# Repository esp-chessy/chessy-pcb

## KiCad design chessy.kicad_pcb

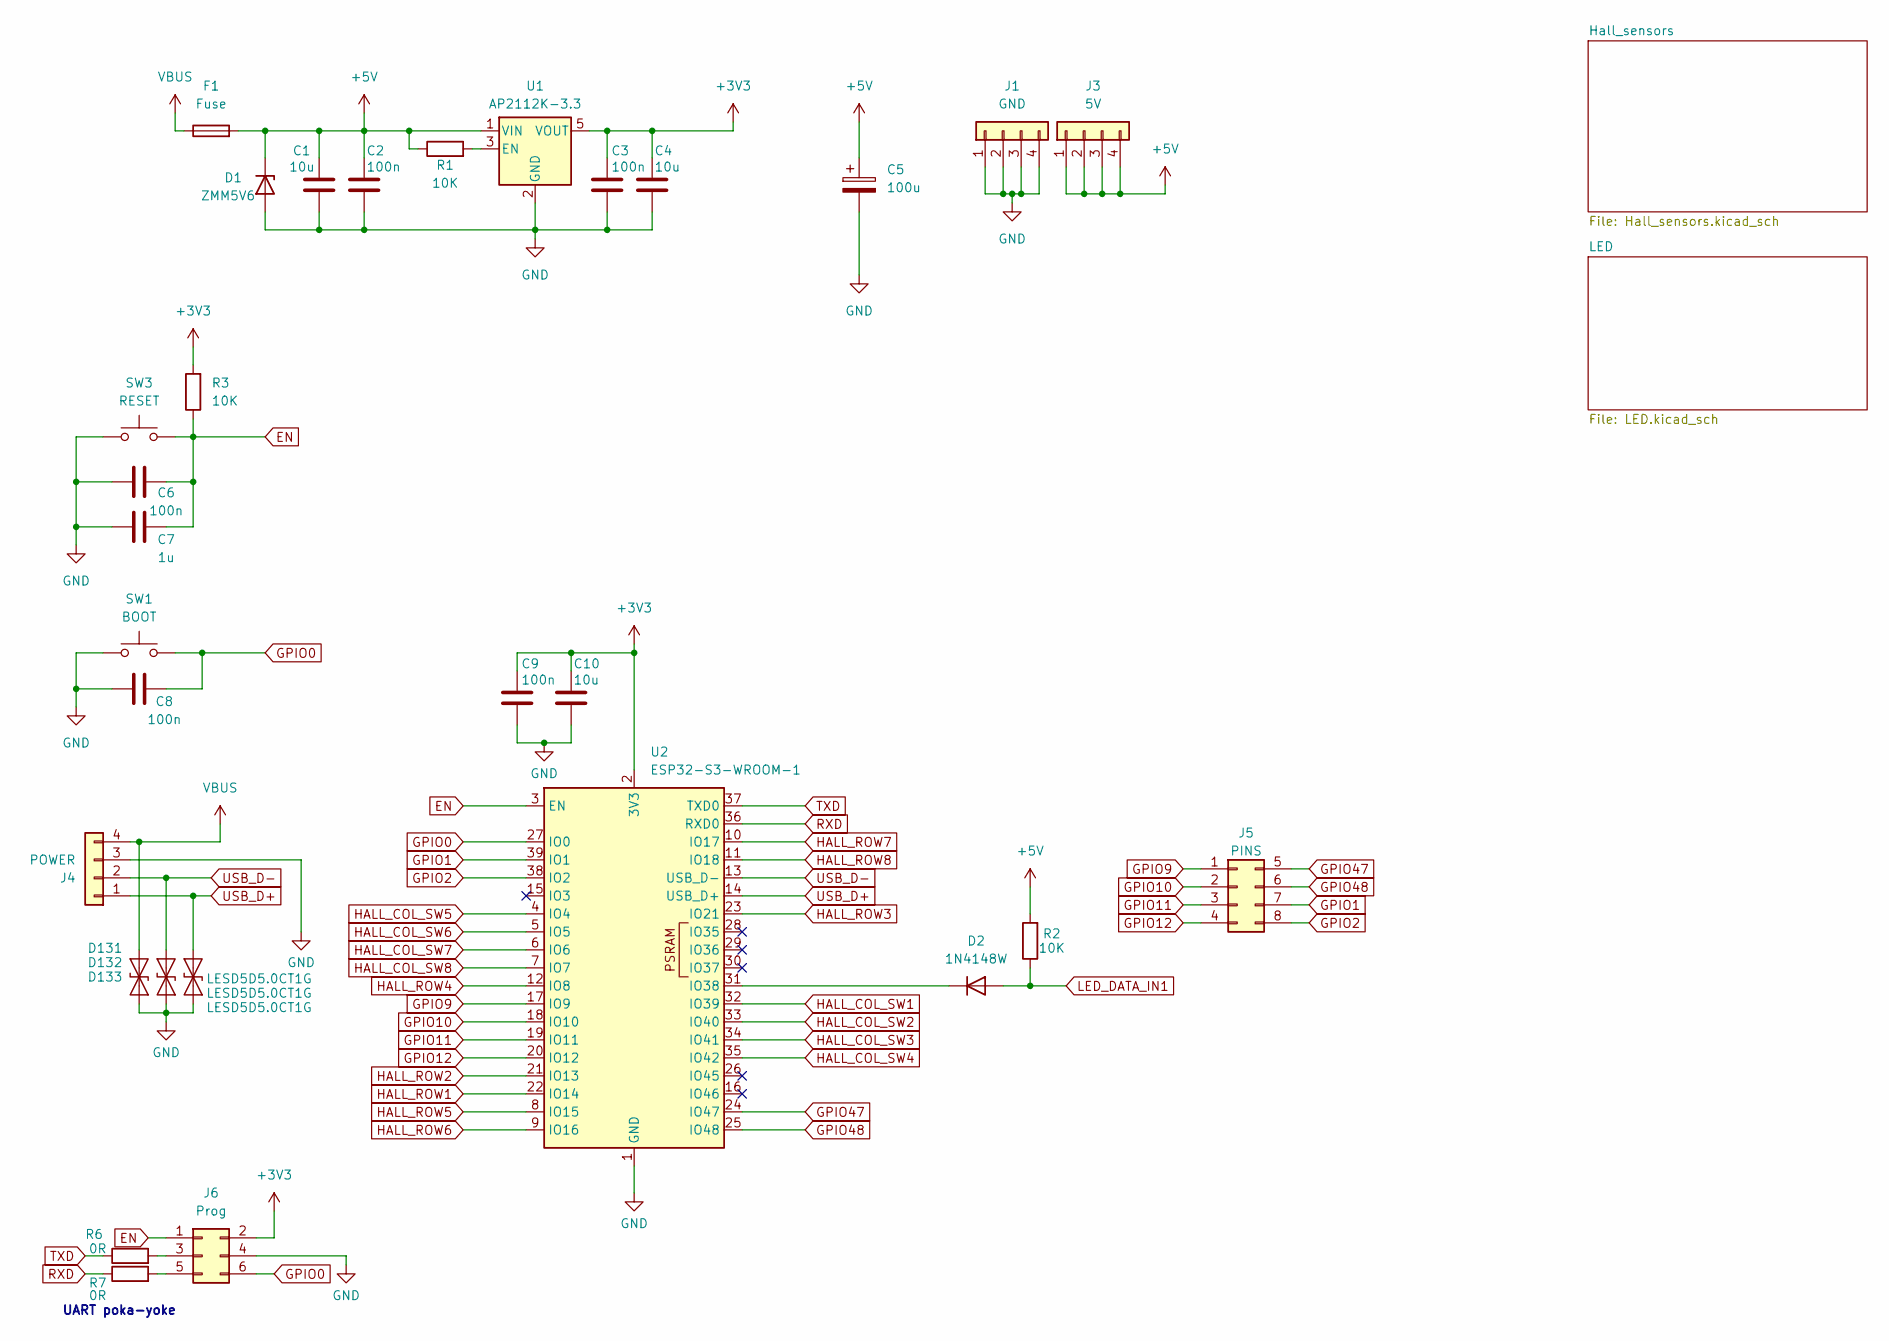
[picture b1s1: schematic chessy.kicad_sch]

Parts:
C1, C4, C10: 10u; C_0805_2012Metric_Pad1.18x1.45mm_HandSolder
C2, C3, C6, C8, C9: 100n; C_0805_2012Metric_Pad1.18x1.45mm_HandSolder
C5: 100u; CP_Radial_D6.3mm_P2.50mm
C7: 1u; C_0805_2012Metric_Pad1.18x1.45mm_HandSolder
D1: ZMM5V6; D_MiniMELF_Handsoldering
D2: 1N4148W; D_SOD-123
D131, D132, D133: LESD5D5.0CT1G; D_SOD-523
F1: Fuse; Fuseholder_Littelfuse_Nano2_154x
J1: GND; PinHeader_1x04_P2.54mm_Vertical
J3: 5V; PinHeader_1x04_P2.54mm_Vertical
J4: POWER; JST_XH_B4B-XH-A_1x04_P2.50mm_Vertical
J5: PINS; PinHeader_2x04_P2.54mm_Vertical
J6: Prog; PinHeader_2x03_P2.54mm_Vertical
R1, R2, R3: 10K; R_0805_2012Metric_Pad1.20x1.40mm_HandSolder
R6, R7: 0R; R_0805_2012Metric_Pad1.20x1.40mm_HandSolder
SW1: BOOT; SW_Push_SPST_NO_Alps_SKRK
SW3: RESET; SW_Push_SPST_NO_Alps_SKRK
U1: AP2112K-3.3; SOT-23-5
U2: ESP32-S3-WROOM-1

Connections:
+3V3: C3.1, C4.1, C9.1, C10.1, J6.2, R3.2, U1.5 (VOUT), U2.2 (3V3); also elsewhere on the board
+5V: C1.1, C2.1, C5.1, D1.1 (K), F1.2, J3.1, J3.2, J3.3, J3.4, R1.1, R2.2, U1.1 (VIN); also elsewhere on the board
EN: C6.2, C7.2, J6.1, R3.1, SW3.2, U2.3 (EN)
GND: C1.2, C2.2, C3.2, C4.2, C5.2, C6.1, C7.1, C8.1, C9.2, C10.2, D1.2 (A), D131.1 (A1), D132.1 (A1), D133.1 (A1), J1.1, J1.2, J1.3, J1.4, J4.3, J6.4, SW1.1, SW3.1, U1.2 (GND), U2.1 (GND), U2.40 (GND), U2.41 (GND); also elsewhere on the board
GPIO0: C8.2, J6.6, SW1.2, U2.27 (IO0)
GPIO1: J5.7, U2.39 (IO1)
GPIO2: J5.8, U2.38 (IO2)
GPIO9: J5.1, U2.17 (IO9)
GPIO10: J5.2, U2.18 (IO10)
GPIO11: J5.3, U2.19 (IO11)
GPIO12: J5.4, U2.20 (IO12)
GPIO47: J5.5, U2.24 (IO47)
GPIO48: J5.6, U2.25 (IO48)
HALL_COL_SW1: U2.32 (IO39); also elsewhere on the board
HALL_COL_SW2: U2.33 (IO40); also elsewhere on the board
HALL_COL_SW3: U2.34 (IO41); also elsewhere on the board
HALL_COL_SW4: U2.35 (IO42); also elsewhere on the board
HALL_COL_SW5: U2.4 (IO4); also elsewhere on the board
HALL_COL_SW6: U2.5 (IO5); also elsewhere on the board
HALL_COL_SW7: U2.6 (IO6); also elsewhere on the board
HALL_COL_SW8: U2.7 (IO7); also elsewhere on the board
HALL_ROW1: U2.22 (IO14); also elsewhere on the board
HALL_ROW2: U2.21 (IO13); also elsewhere on the board
HALL_ROW3: U2.23 (IO21); also elsewhere on the board
HALL_ROW4: U2.12 (IO8); also elsewhere on the board
HALL_ROW5: U2.8 (IO15); also elsewhere on the board
HALL_ROW6: U2.9 (IO16); also elsewhere on the board
HALL_ROW7: U2.10 (IO17); also elsewhere on the board
HALL_ROW8: U2.11 (IO18); also elsewhere on the board
LED_DATA_IN1: D2.2 (A), R2.1; also elsewhere on the board
unnamed: D2.1 (K), U2.31 (IO38)
unnamed: J6.3, R6.2
unnamed: J6.5, R7.2
unnamed: R1.2, U1.3 (EN)
RXD: R7.1, U2.36 (RXD0)
TXD: R6.1, U2.37 (TXD0)
USB_D+: D133.2 (A2), J4.1, U2.14 (USB_D+)
USB_D-: D132.2 (A2), J4.2, U2.13 (USB_D-)
VBUS: D131.2 (A2), F1.1, J4.4

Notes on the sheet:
UART poka-yoke

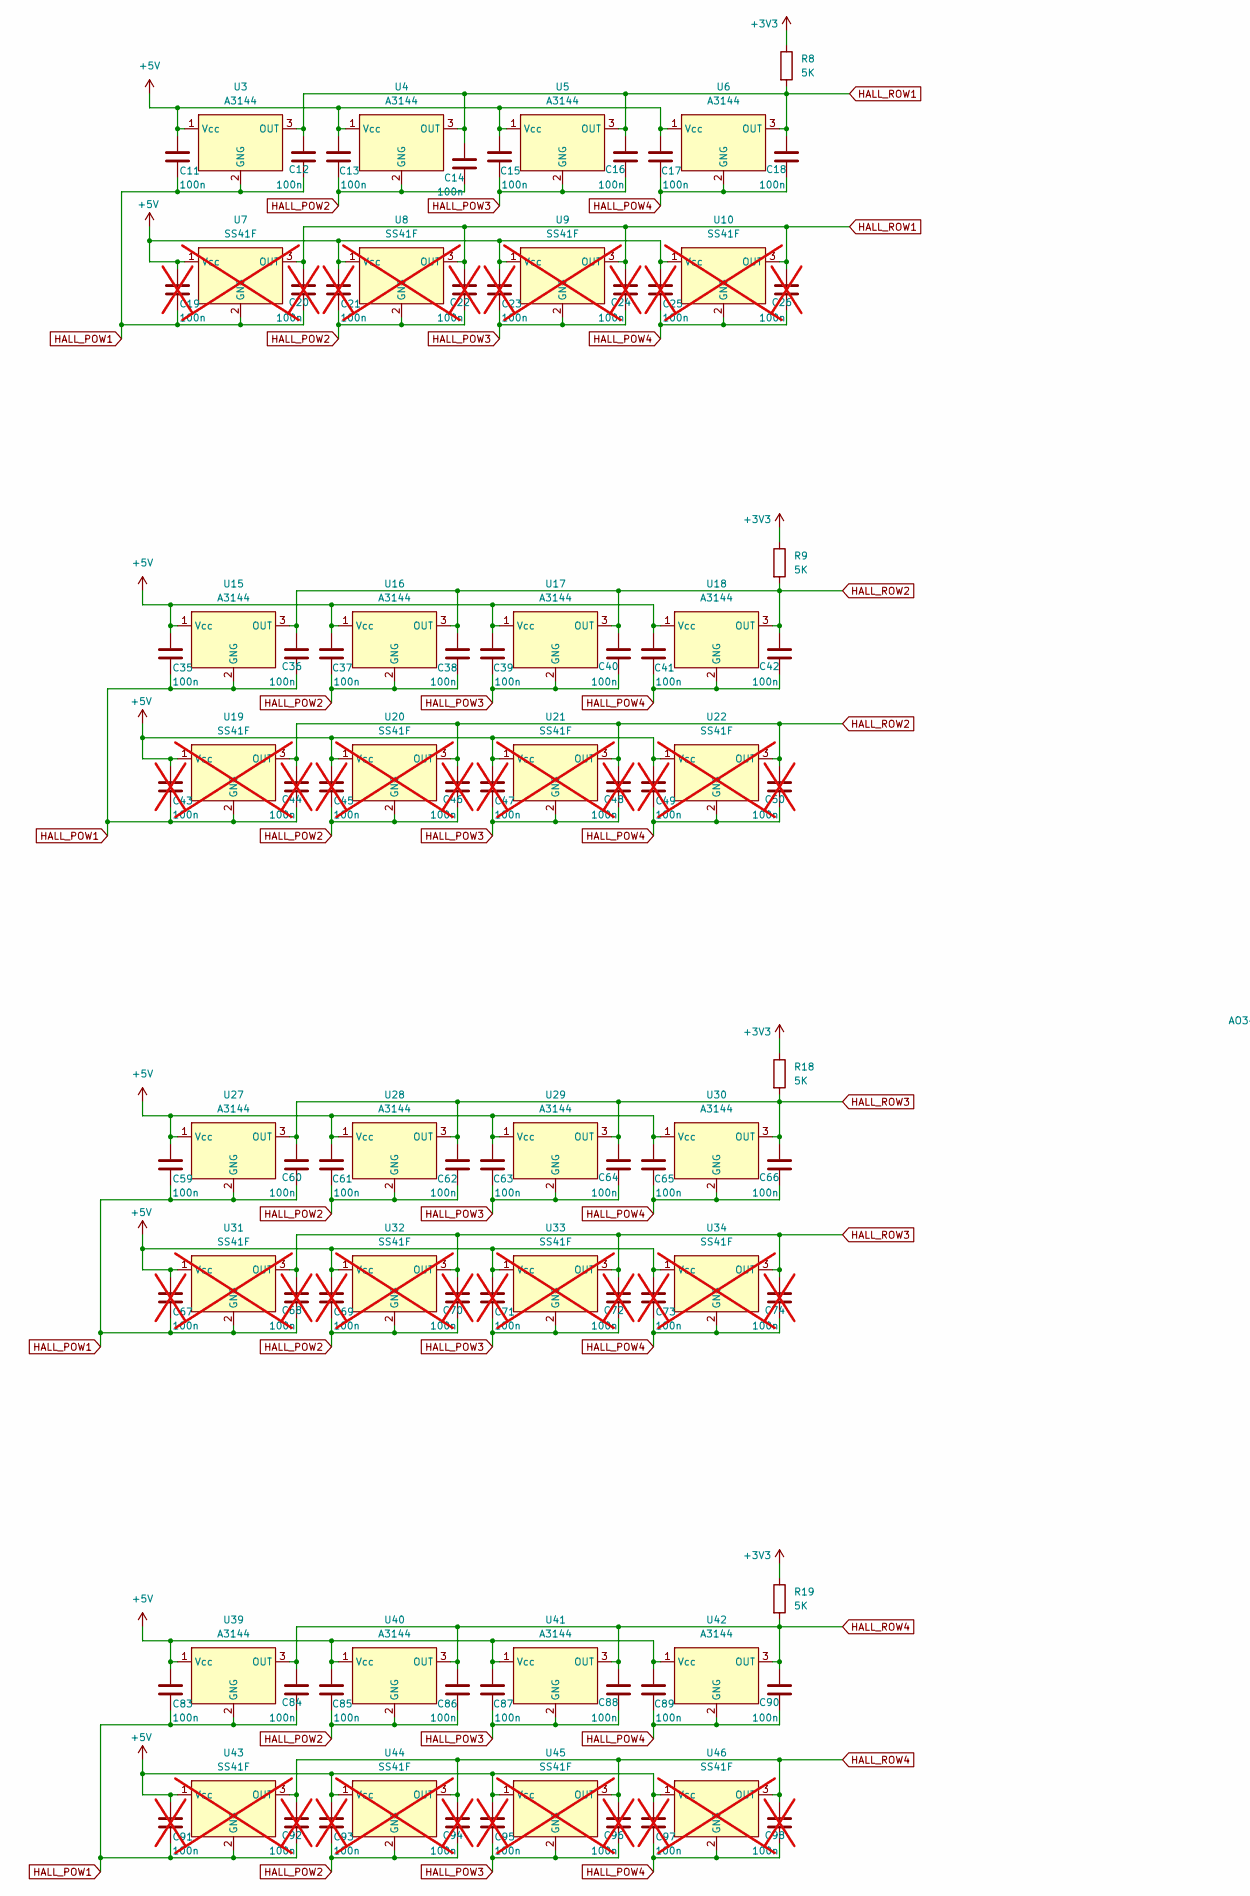
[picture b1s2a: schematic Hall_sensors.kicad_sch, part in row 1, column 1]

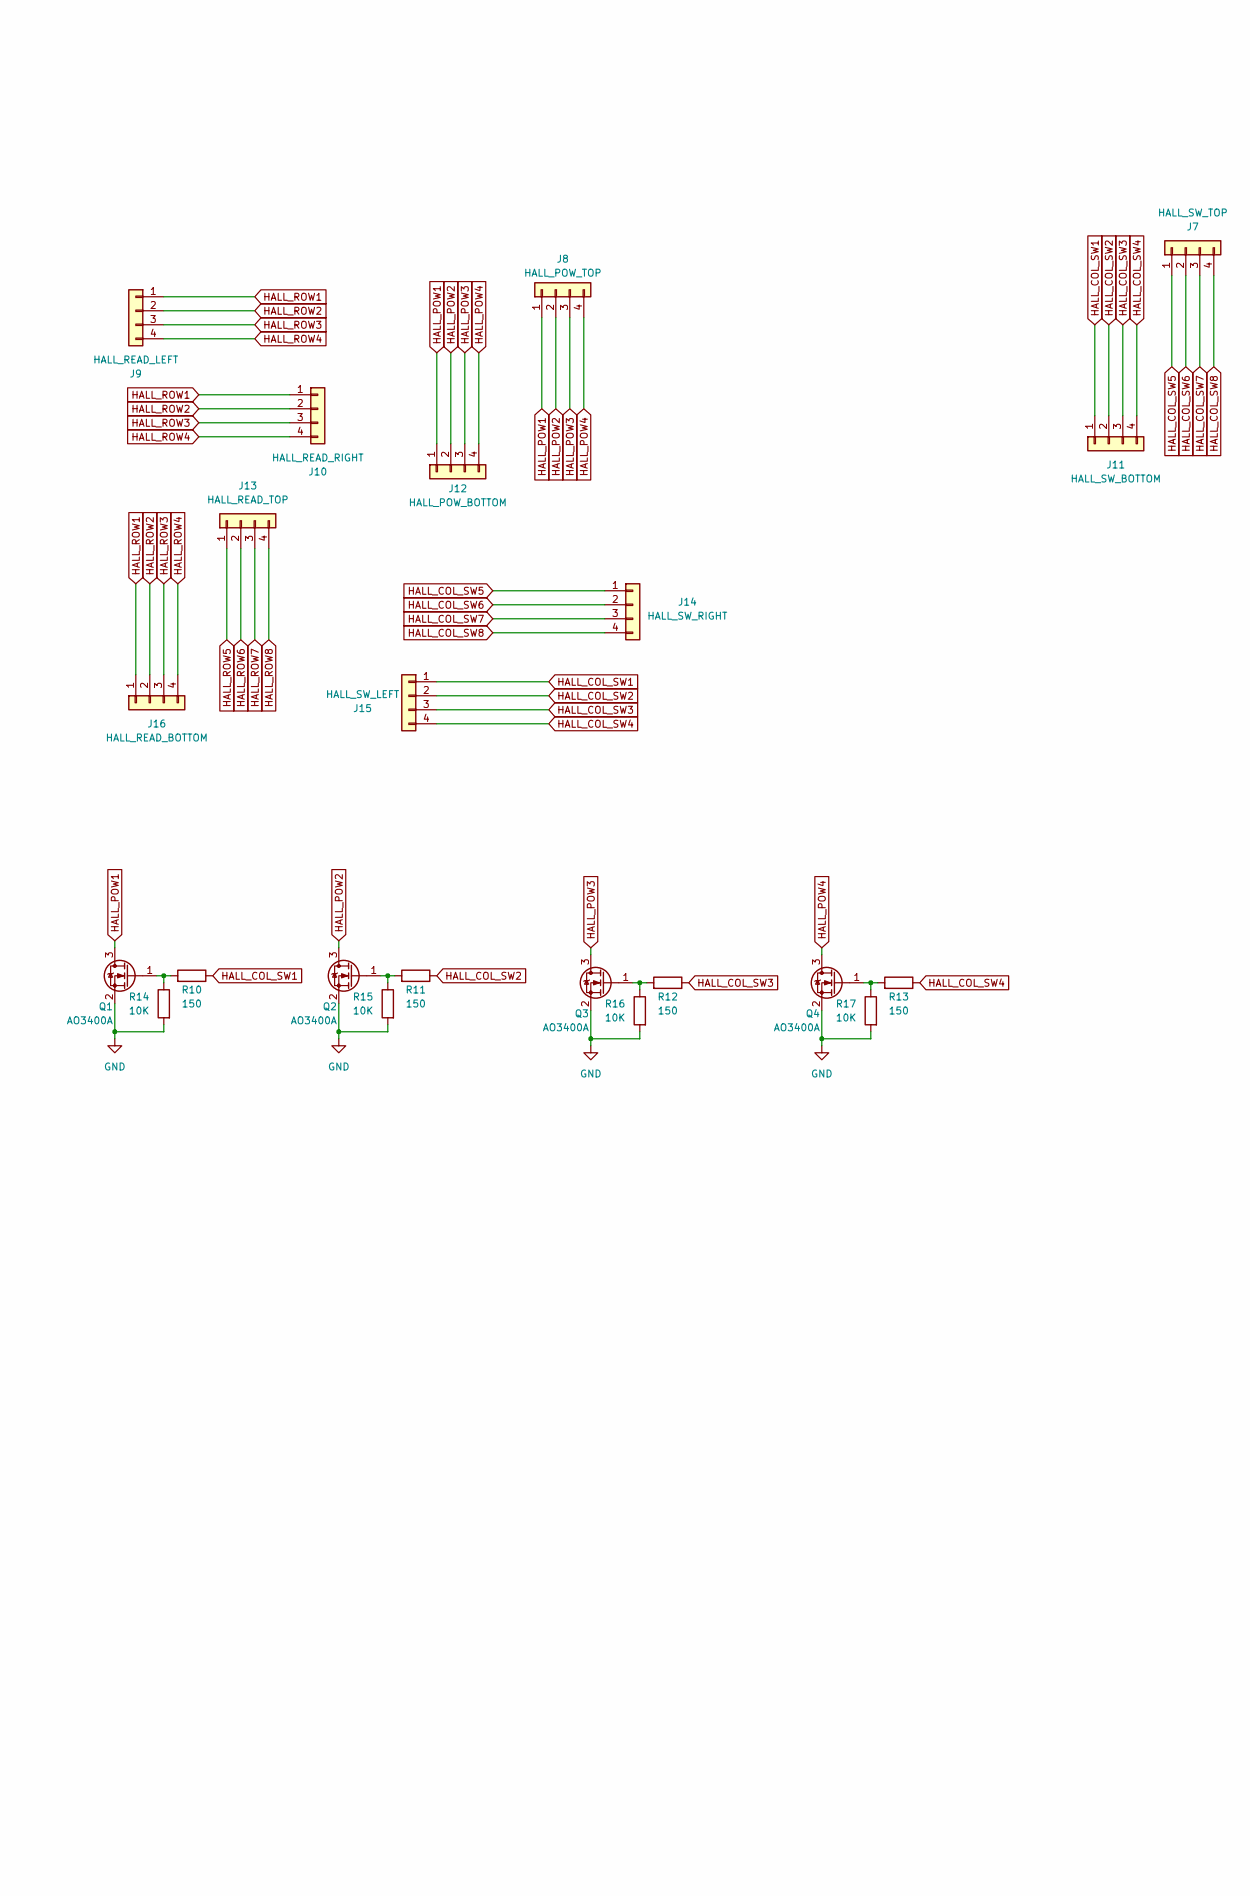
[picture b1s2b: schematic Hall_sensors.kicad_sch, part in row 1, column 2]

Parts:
C11, C12, C13, C14, C15, C16, C17, C18, C35, C36, C37, C38, C39, C40, C41, C42, C59, C60, C61, C62, C63, C64, C65, C66, C83, C84, C85, C86, C87, C88, C89, C90: 100n; C_0805_2012Metric_Pad1.18x1.45mm_HandSolder
C19, C20, C21, C22, C23, C24, C25, C26, C43, C44, C45, C46, C47, C48, C49, C50, C67, C68, C69, C70, C71, C72, C73, C74, C91, C92, C93, C94, C95, C96, C97, C98: 100n; C_0805_2012Metric_Pad1.18x1.45mm_HandSolder; not fitted
J7: HALL_SW_TOP; Harwin_M20-89004xx_1x04_P2.54mm_Horizontal
J8: HALL_POW_TOP; Harwin_M20-89004xx_1x04_P2.54mm_Horizontal
J9: HALL_READ_LEFT; Harwin_M20-89004xx_1x04_P2.54mm_Horizontal
J10: HALL_READ_RIGHT; Harwin_M20-89004xx_1x04_P2.54mm_Horizontal
J11: HALL_SW_BOTTOM; Harwin_M20-89004xx_1x04_P2.54mm_Horizontal
J12: HALL_POW_BOTTOM; Harwin_M20-89004xx_1x04_P2.54mm_Horizontal
J13: HALL_READ_TOP; Harwin_M20-89004xx_1x04_P2.54mm_Horizontal
J14: HALL_SW_RIGHT; Harwin_M20-89004xx_1x04_P2.54mm_Horizontal
J15: HALL_SW_LEFT; Harwin_M20-89004xx_1x04_P2.54mm_Horizontal
J16: HALL_READ_BOTTOM; Harwin_M20-89004xx_1x04_P2.54mm_Horizontal
Q1, Q2, Q3, Q4: AO3400A; SOT-23
R8, R9, R18, R19: 5K; R_0805_2012Metric_Pad1.20x1.40mm_HandSolder
R10, R11, R12, R13: 150; R_0805_2012Metric_Pad1.20x1.40mm_HandSolder
R14, R15, R16, R17: 10K; R_0805_2012Metric_Pad1.20x1.40mm_HandSolder
U3, U4, U5, U6, U15, U16, U17, U18, U27, U28, U29, U30, U39, U40, U41, U42: A3144; TO-92Flat
U7, U8, U9, U10, U19, U20, U21, U22, U31, U32, U33, U34, U43, U44, U45, U46: SS41F; SOT-23; not fitted

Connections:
+3V3: R8.1, R9.1, R18.1, R19.1; also elsewhere on the board
+5V: C11.1, C13.1, C15.1, C17.1, C19.1, C21.1, C23.1, C25.1, C35.1, C37.1, C39.1, C41.1, C43.1, C45.1, C47.1, C49.1, C59.1, C61.1, C63.1, C65.1, C67.1, C69.1, C71.1, C73.1, C83.1, C85.1, C87.1, C89.1, C91.1, C93.1, C95.1, C97.1, U3.1 (Vcc), U4.1 (Vcc), U5.1 (Vcc), U6.1 (Vcc), U7.1 (Vcc), U8.1 (Vcc), U9.1 (Vcc), U10.1 (Vcc), U15.1 (Vcc), U16.1 (Vcc), U17.1 (Vcc), U18.1 (Vcc), U19.1 (Vcc), U20.1 (Vcc), U21.1 (Vcc), U22.1 (Vcc), U27.1 (Vcc), U28.1 (Vcc), U29.1 (Vcc), U30.1 (Vcc), U31.1 (Vcc), U32.1 (Vcc), U33.1 (Vcc), U34.1 (Vcc), U39.1 (Vcc), U40.1 (Vcc), U41.1 (Vcc), U42.1 (Vcc), U43.1 (Vcc), U44.1 (Vcc), U45.1 (Vcc), U46.1 (Vcc); also elsewhere on the board
GND: Q1.2 (S), Q2.2 (S), Q3.2 (S), Q4.2 (S), R14.2, R15.2, R16.2, R17.2; also elsewhere on the board
HALL_COL_SW1: J11.1, J15.1, R10.1; also elsewhere on the board
HALL_COL_SW2: J11.2, J15.2, R11.1; also elsewhere on the board
HALL_COL_SW3: J11.3, J15.3, R12.1; also elsewhere on the board
HALL_COL_SW4: J11.4, J15.4, R13.1; also elsewhere on the board
HALL_COL_SW5: J7.1, J14.1; also elsewhere on the board
HALL_COL_SW6: J7.2, J14.2; also elsewhere on the board
HALL_COL_SW7: J7.3, J14.3; also elsewhere on the board
HALL_COL_SW8: J7.4, J14.4; also elsewhere on the board
HALL_POW1: C11.2, C12.2, C19.2, C20.2, C35.2, C36.2, C43.2, C44.2, C59.2, C60.2, C67.2, C68.2, C83.2, C84.2, C91.2, C92.2, J8.1, J12.1, Q1.3 (D), U3.2 (GNG), U7.2 (GNG), U15.2 (GNG), U19.2 (GNG), U27.2 (GNG), U31.2 (GNG), U39.2 (GNG), U43.2 (GNG)
HALL_POW2: C13.2, C14.2, C21.2, C22.2, C37.2, C38.2, C45.2, C46.2, C61.2, C62.2, C69.2, C70.2, C85.2, C86.2, C93.2, C94.2, J8.2, J12.2, Q2.3 (D), U4.2 (GNG), U8.2 (GNG), U16.2 (GNG), U20.2 (GNG), U28.2 (GNG), U32.2 (GNG), U40.2 (GNG), U44.2 (GNG)
HALL_POW3: C15.2, C16.2, C23.2, C24.2, C39.2, C40.2, C47.2, C48.2, C63.2, C64.2, C71.2, C72.2, C87.2, C88.2, C95.2, C96.2, J8.3, J12.3, Q3.3 (D), U5.2 (GNG), U9.2 (GNG), U17.2 (GNG), U21.2 (GNG), U29.2 (GNG), U33.2 (GNG), U41.2 (GNG), U45.2 (GNG)
HALL_POW4: C17.2, C18.2, C25.2, C26.2, C41.2, C42.2, C49.2, C50.2, C65.2, C66.2, C73.2, C74.2, C89.2, C90.2, C97.2, C98.2, J8.4, J12.4, Q4.3 (D), U6.2 (GNG), U10.2 (GNG), U18.2 (GNG), U22.2 (GNG), U30.2 (GNG), U34.2 (GNG), U42.2 (GNG), U46.2 (GNG)
HALL_ROW1: C12.1, C14.1, C16.1, C18.1, C20.1, C22.1, C24.1, C26.1, J9.1, J10.1, J16.1, R8.2, U3.3 (OUT), U4.3 (OUT), U5.3 (OUT), U6.3 (OUT), U7.3 (OUT), U8.3 (OUT), U9.3 (OUT), U10.3 (OUT); also elsewhere on the board
HALL_ROW2: C36.1, C38.1, C40.1, C42.1, C44.1, C46.1, C48.1, C50.1, J9.2, J10.2, J16.2, R9.2, U15.3 (OUT), U16.3 (OUT), U17.3 (OUT), U18.3 (OUT), U19.3 (OUT), U20.3 (OUT), U21.3 (OUT), U22.3 (OUT); also elsewhere on the board
HALL_ROW3: C60.1, C62.1, C64.1, C66.1, C68.1, C70.1, C72.1, C74.1, J9.3, J10.3, J16.3, R18.2, U27.3 (OUT), U28.3 (OUT), U29.3 (OUT), U30.3 (OUT), U31.3 (OUT), U32.3 (OUT), U33.3 (OUT), U34.3 (OUT); also elsewhere on the board
HALL_ROW4: C84.1, C86.1, C88.1, C90.1, C92.1, C94.1, C96.1, C98.1, J9.4, J10.4, J16.4, R19.2, U39.3 (OUT), U40.3 (OUT), U41.3 (OUT), U42.3 (OUT), U43.3 (OUT), U44.3 (OUT), U45.3 (OUT), U46.3 (OUT); also elsewhere on the board
HALL_ROW5: J13.1; also elsewhere on the board
HALL_ROW6: J13.2; also elsewhere on the board
HALL_ROW7: J13.3; also elsewhere on the board
HALL_ROW8: J13.4; also elsewhere on the board
unnamed: Q1.1 (G), R10.2, R14.1
unnamed: Q2.1 (G), R11.2, R15.1
unnamed: Q3.1 (G), R12.2, R16.1
unnamed: Q4.1 (G), R13.2, R17.1

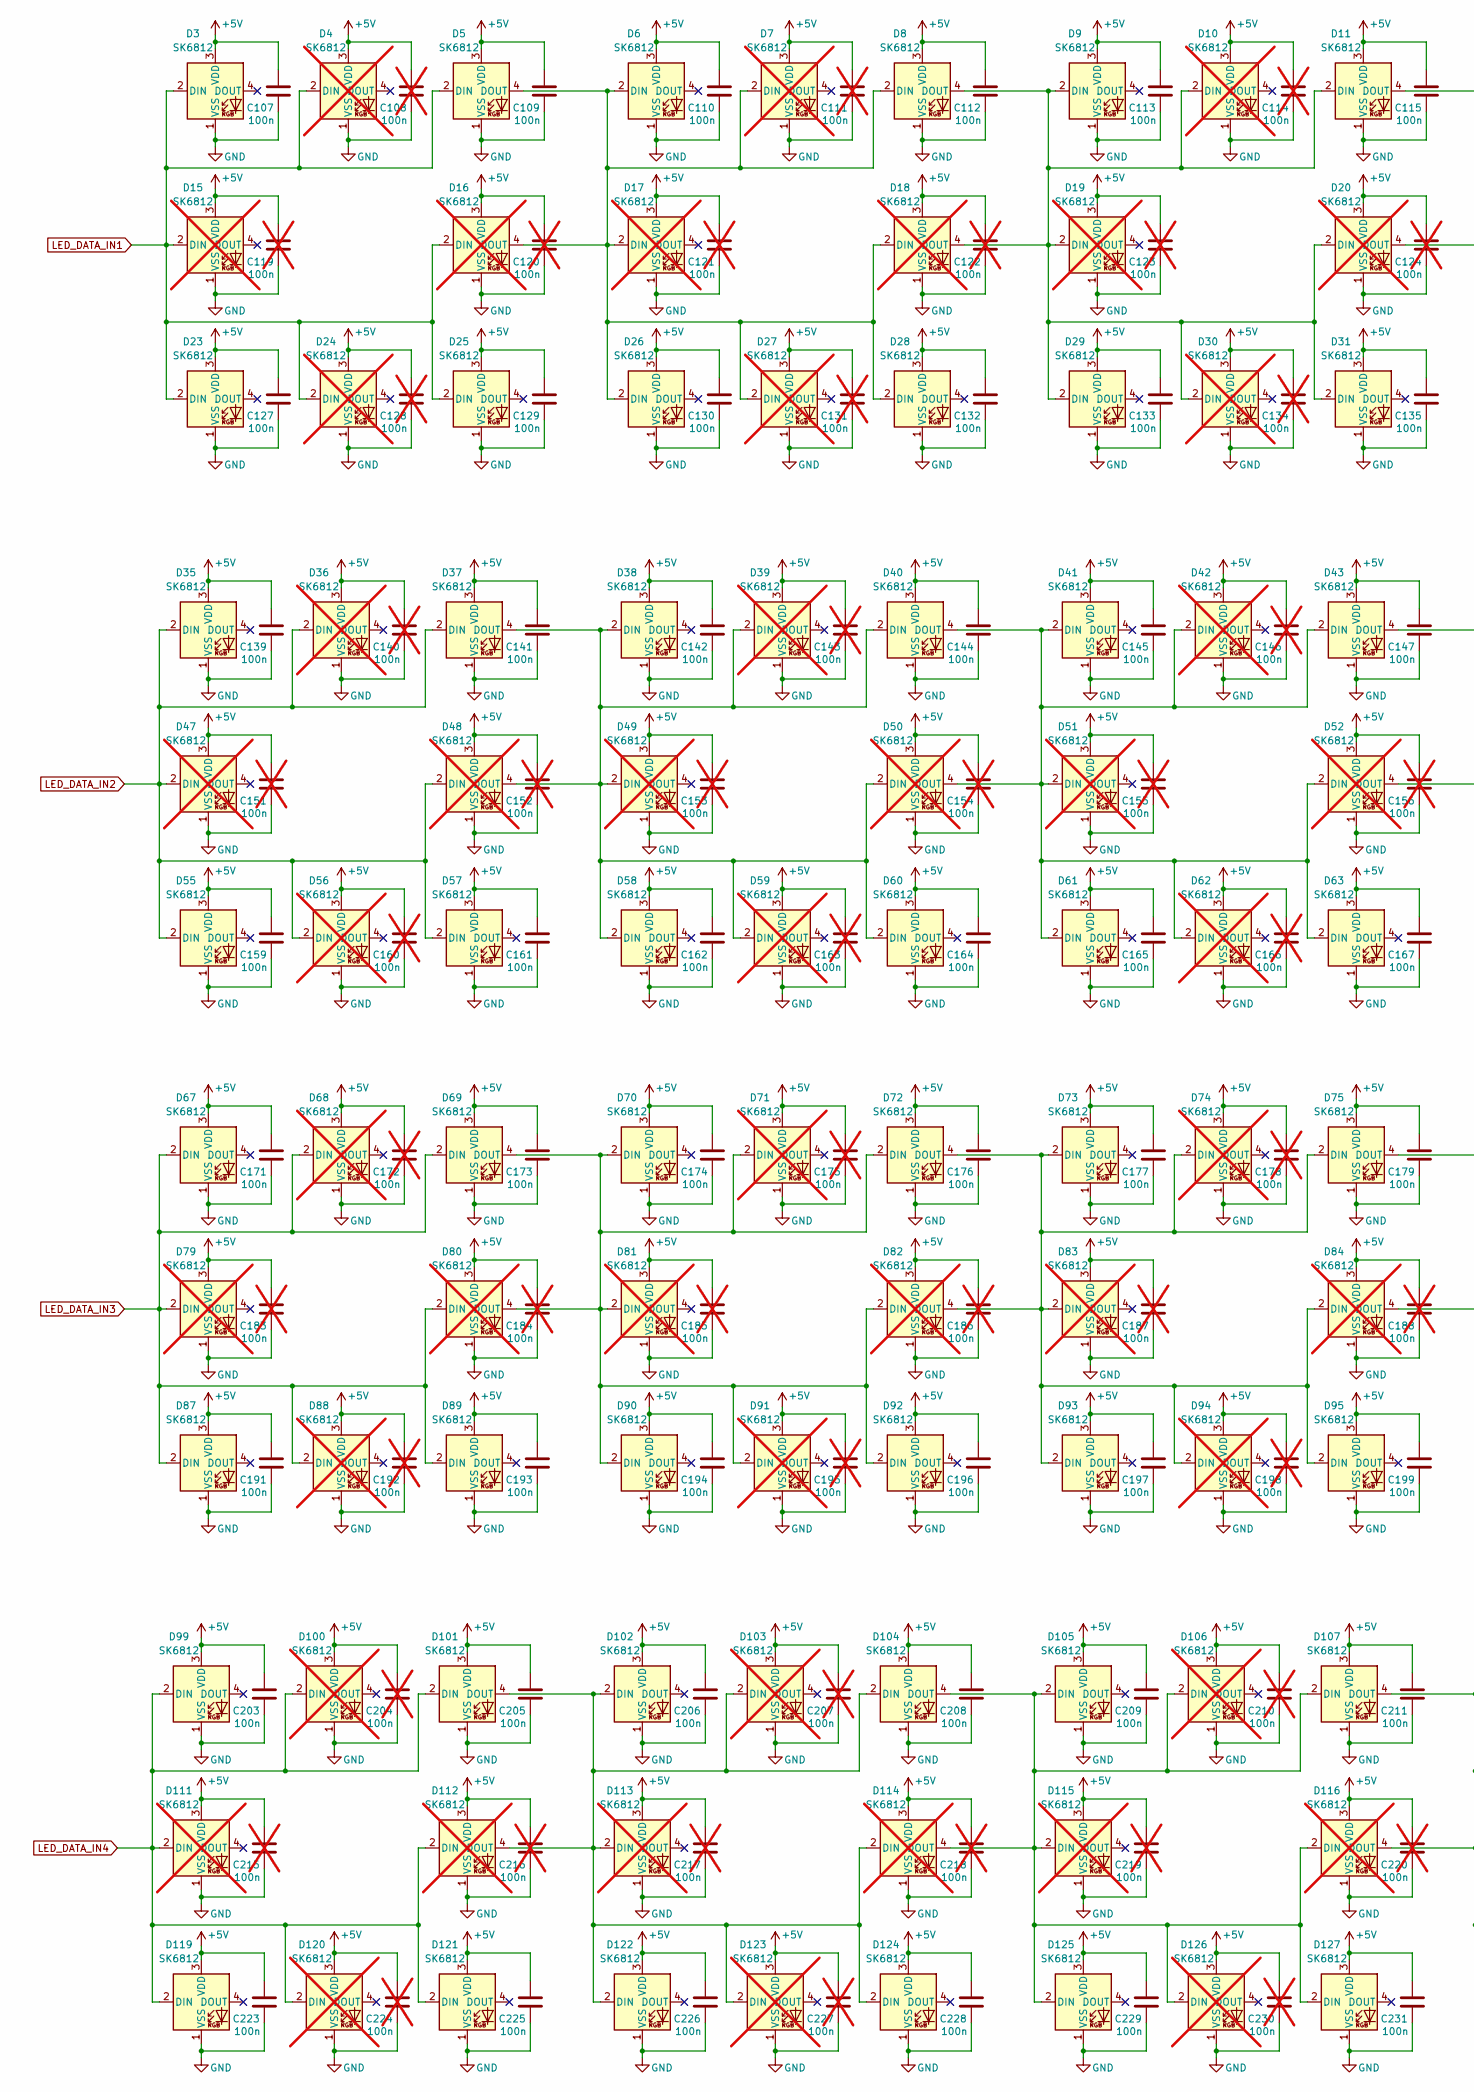
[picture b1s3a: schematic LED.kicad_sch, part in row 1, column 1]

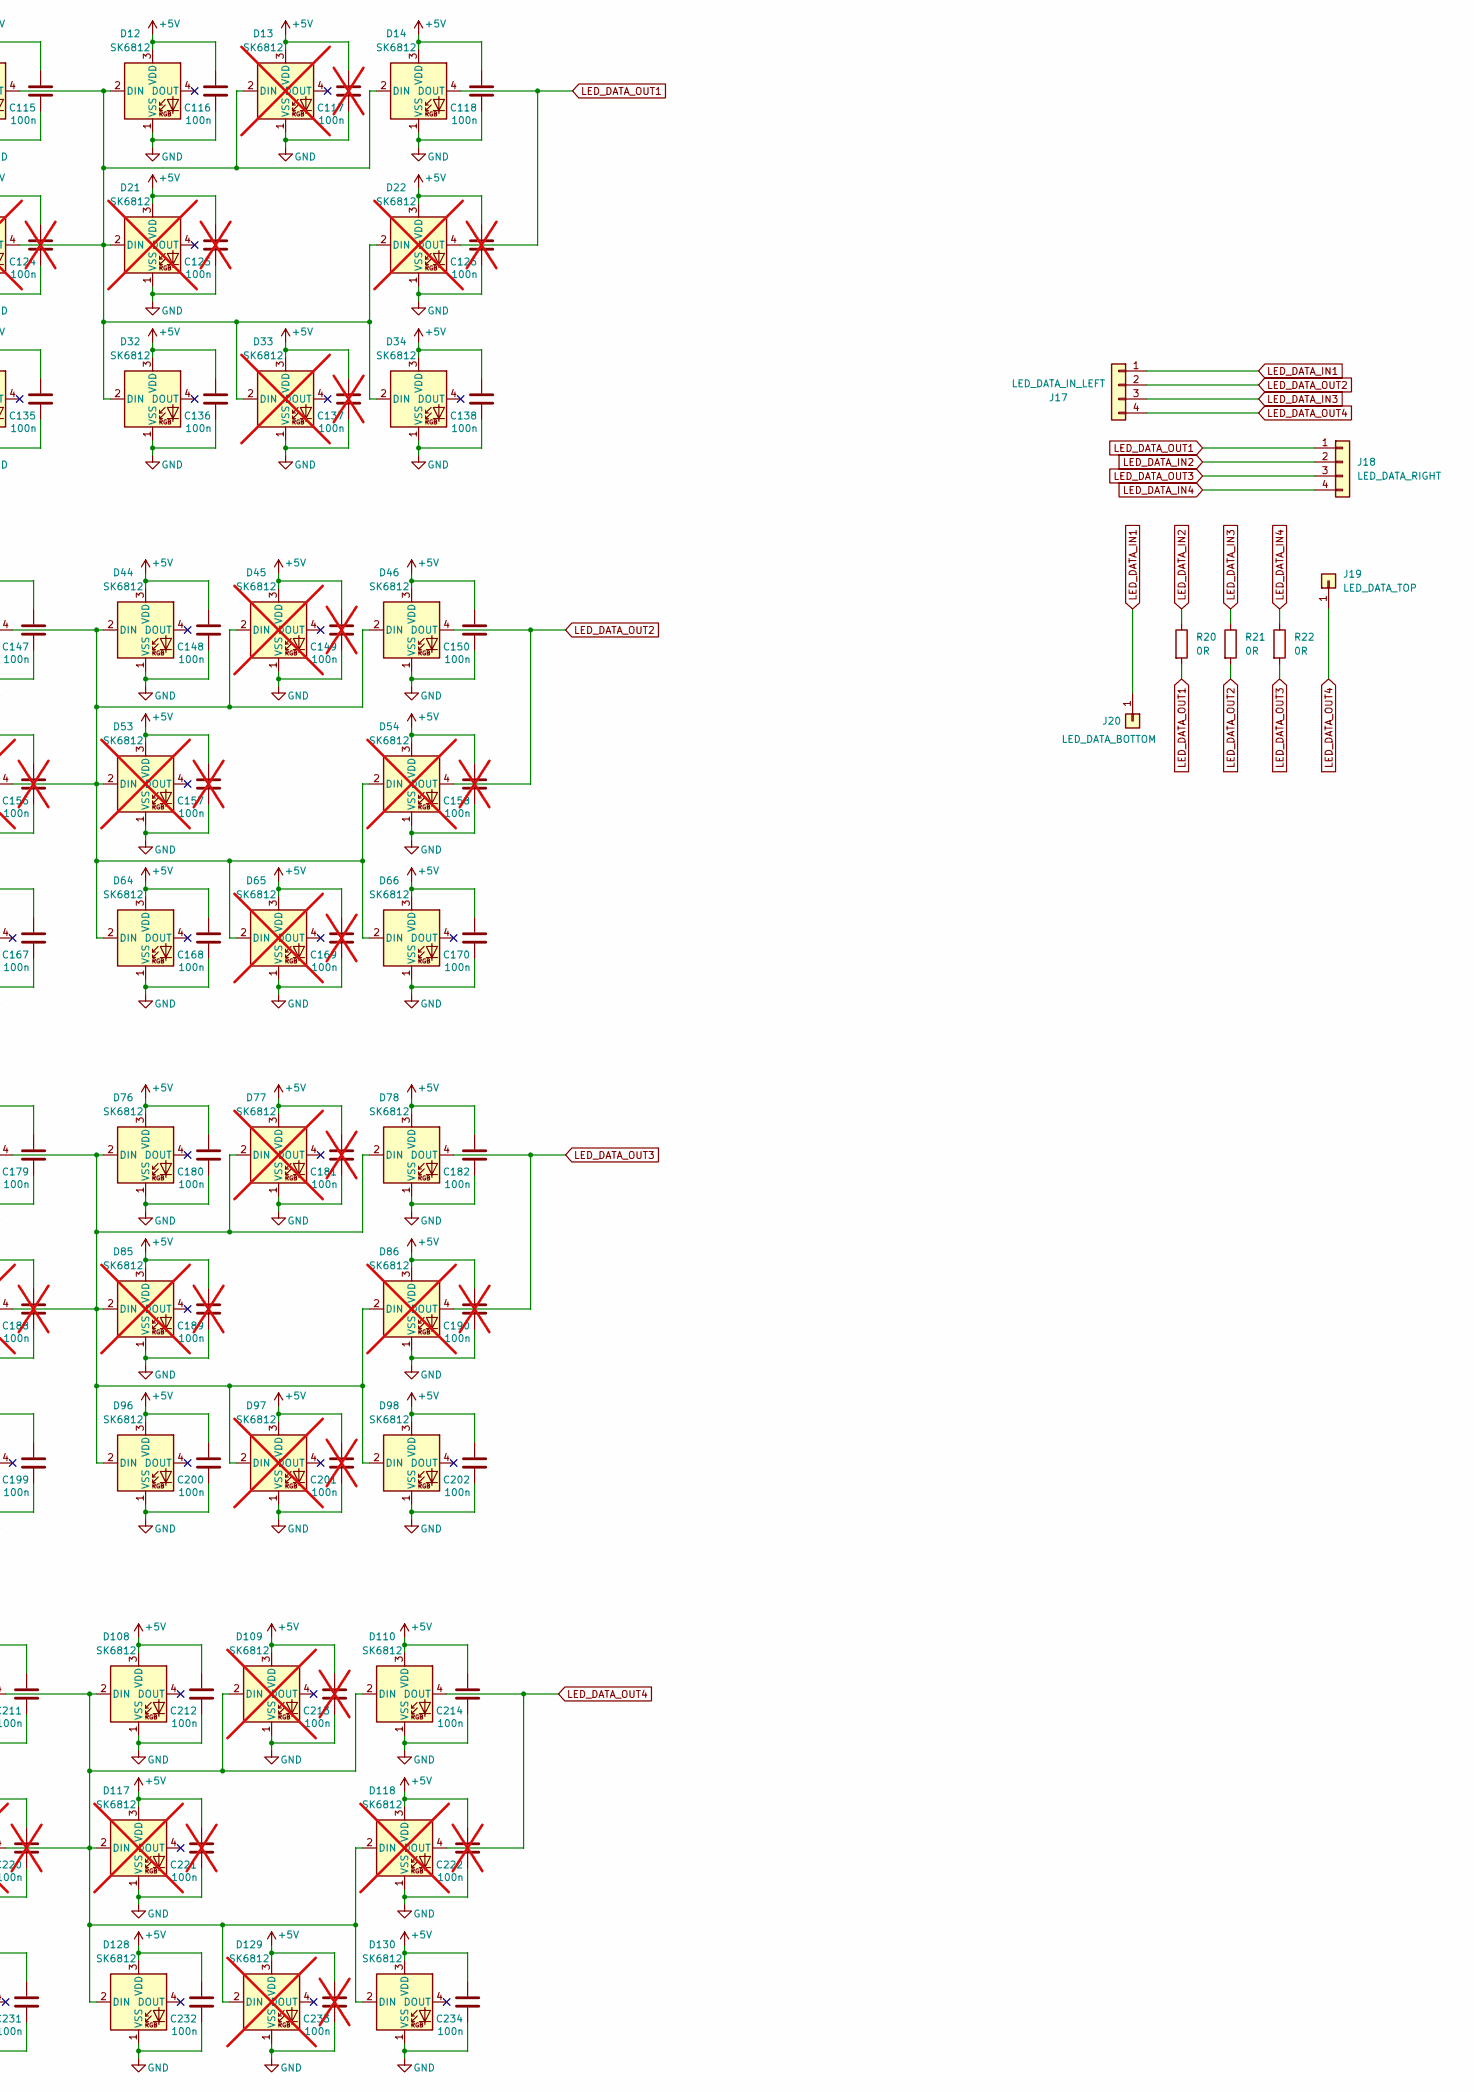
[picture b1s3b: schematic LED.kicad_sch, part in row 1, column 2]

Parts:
C107, C109, C110, C112, C113, C115, C116, C118, C127, C129, C130, C132, C133, C135, C136, C138, C139, C141, C142, C144, C145, C147, C148, C150, C159, C161, C162, C164, C165, C167, C168, C170, C171, C173, C174, C176, C177, C179, C180, C182, C191, C193, C194, C196, C197, C199, C200, C202, C203, C205, C206, C208, C209, C211, C212, C214, C223, C225, C226, C228, C229, C231, C232, C234: 100n; C_0805_2012Metric_Pad1.18x1.45mm_HandSolder
C108, C111, C114, C117, C119, C120, C121, C122, C123, C124, C125, C126, C128, C131, C134, C137, C140, C143, C146, C149, C151, C152, C153, C154, C155, C156, C157, C158, C160, C163, C166, C169, C172, C175, C178, C181, C183, C184, C185, C186, C187, C188, C189, C190, C192, C195, C198, C201, C204, C207, C210, C213, C215, C216, C217, C218, C219, C220, C221, C222, C224, C227, C230, C233: 100n; C_0805_2012Metric_Pad1.18x1.45mm_HandSolder; not fitted
D3, D5, D6, D8, D9, D11, D12, D14, D23, D25, D26, D28, D29, D31, D32, D34, D35, D37, D38, D40, D41, D43, D44, D46, D55, D57, D58, D60, D61, D63, D64, D66, D67, D69, D70, D72, D73, D75, D76, D78, D87, D89, D90, D92, D93, D95, D96, D98, D99, D101, D102, D104, D105, D107, D108, D110, D119, D121, D122, D124, D125, D127, D128, D130: SK6812; LED_SK6812_PLCC4_5.0x5.0mm_P3.2mm
D4, D7, D10, D13, D15, D16, D17, D18, D19, D20, D21, D22, D24, D27, D30, D33, D36, D39, D42, D45, D47, D48, D49, D50, D51, D52, D53, D54, D56, D59, D62, D65, D68, D71, D74, D77, D79, D80, D81, D82, D83, D84, D85, D86, D88, D91, D94, D97, D100, D103, D106, D109, D111, D112, D113, D114, D115, D116, D117, D118, D120, D123, D126, D129: SK6812; LED_SK6812_PLCC4_5.0x5.0mm_P3.2mm; not fitted
J17: LED_DATA_IN_LEFT; Harwin_M20-89004xx_1x04_P2.54mm_Horizontal
J18: LED_DATA_RIGHT; Harwin_M20-89004xx_1x04_P2.54mm_Horizontal
J19: LED_DATA_TOP; SolderWirePad_1x01_SMD_1x2mm
J20: LED_DATA_BOTTOM; SolderWirePad_1x01_SMD_1x2mm
R20, R21, R22: 0R; R_0805_2012Metric_Pad1.20x1.40mm_HandSolder

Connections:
+5V: C107.1, C108.1, C109.1, C110.1, C111.1, C112.1, C113.1, C114.1, C115.1, C116.1, C117.1, C118.1, C119.1, C120.1, C121.1, C122.1, C123.1, C124.1, C125.1, C126.1, C127.1, C128.1, C129.1, C130.1, C131.1, C132.1, C133.1, C134.1, C135.1, C136.1, C137.1, C138.1, C139.1, C140.1, C141.1, C142.1, C143.1, C144.1, C145.1, C146.1, C147.1, C148.1, C149.1, C150.1, C151.1, C152.1, C153.1, C154.1, C155.1, C156.1, C157.1, C158.1, C159.1, C160.1, C161.1, C162.1, C163.1, C164.1, C165.1, C166.1, C167.1, C168.1, C169.1, C170.1, C171.1, C172.1, C173.1, C174.1, C175.1, C176.1, C177.1, C178.1, C179.1, C180.1, C181.1, C182.1, C183.1, C184.1, C185.1, C186.1, C187.1, C188.1, C189.1, C190.1, C191.1, C192.1, C193.1, C194.1, C195.1, C196.1, C197.1, C198.1, C199.1, C200.1, C201.1, C202.1, C203.1, C204.1, C205.1, C206.1, C207.1, C208.1, C209.1, C210.1, C211.1, C212.1, C213.1, C214.1, C215.1, C216.1, C217.1, C218.1, C219.1, C220.1, C221.1, C222.1, C223.1, C224.1, C225.1, C226.1, C227.1, C228.1, C229.1, C230.1, C231.1, C232.1, C233.1, C234.1, D3.3 (VDD), D4.3 (VDD), D5.3 (VDD), D6.3 (VDD), D7.3 (VDD), D8.3 (VDD), D9.3 (VDD), D10.3 (VDD), D11.3 (VDD), D12.3 (VDD), D13.3 (VDD), D14.3 (VDD), D15.3 (VDD), D16.3 (VDD), D17.3 (VDD), D18.3 (VDD), D19.3 (VDD), D20.3 (VDD), D21.3 (VDD), D22.3 (VDD), D23.3 (VDD), D24.3 (VDD), D25.3 (VDD), D26.3 (VDD), D27.3 (VDD), D28.3 (VDD), D29.3 (VDD), D30.3 (VDD), D31.3 (VDD), D32.3 (VDD), D33.3 (VDD), D34.3 (VDD), D35.3 (VDD), D36.3 (VDD), D37.3 (VDD), D38.3 (VDD), D39.3 (VDD), D40.3 (VDD), D41.3 (VDD), D42.3 (VDD), D43.3 (VDD), D44.3 (VDD), D45.3 (VDD), D46.3 (VDD), D47.3 (VDD), D48.3 (VDD), D49.3 (VDD), D50.3 (VDD), D51.3 (VDD), D52.3 (VDD), D53.3 (VDD), D54.3 (VDD), D55.3 (VDD), D56.3 (VDD), D57.3 (VDD), D58.3 (VDD), D59.3 (VDD), D60.3 (VDD), D61.3 (VDD), D62.3 (VDD), D63.3 (VDD), D64.3 (VDD), D65.3 (VDD), D66.3 (VDD), D67.3 (VDD), D68.3 (VDD), D69.3 (VDD), D70.3 (VDD), D71.3 (VDD), D72.3 (VDD), D73.3 (VDD), D74.3 (VDD), D75.3 (VDD), D76.3 (VDD), D77.3 (VDD), D78.3 (VDD), D79.3 (VDD), D80.3 (VDD), D81.3 (VDD), D82.3 (VDD), D83.3 (VDD), D84.3 (VDD), D85.3 (VDD), D86.3 (VDD), D87.3 (VDD), D88.3 (VDD), D89.3 (VDD), D90.3 (VDD), D91.3 (VDD), D92.3 (VDD), D93.3 (VDD), D94.3 (VDD), D95.3 (VDD), D96.3 (VDD), D97.3 (VDD), D98.3 (VDD), D99.3 (VDD), D100.3 (VDD), D101.3 (VDD), D102.3 (VDD), D103.3 (VDD), D104.3 (VDD), D105.3 (VDD), D106.3 (VDD), D107.3 (VDD), D108.3 (VDD), D109.3 (VDD), D110.3 (VDD), D111.3 (VDD), D112.3 (VDD), D113.3 (VDD), D114.3 (VDD), D115.3 (VDD), D116.3 (VDD), D117.3 (VDD), D118.3 (VDD), D119.3 (VDD), D120.3 (VDD), D121.3 (VDD), D122.3 (VDD), D123.3 (VDD), D124.3 (VDD), D125.3 (VDD), D126.3 (VDD), D127.3 (VDD), D128.3 (VDD), D129.3 (VDD), D130.3 (VDD); also elsewhere on the board
GND: C107.2, C108.2, C109.2, C110.2, C111.2, C112.2, C113.2, C114.2, C115.2, C116.2, C117.2, C118.2, C119.2, C120.2, C121.2, C122.2, C123.2, C124.2, C125.2, C126.2, C127.2, C128.2, C129.2, C130.2, C131.2, C132.2, C133.2, C134.2, C135.2, C136.2, C137.2, C138.2, C139.2, C140.2, C141.2, C142.2, C143.2, C144.2, C145.2, C146.2, C147.2, C148.2, C149.2, C150.2, C151.2, C152.2, C153.2, C154.2, C155.2, C156.2, C157.2, C158.2, C159.2, C160.2, C161.2, C162.2, C163.2, C164.2, C165.2, C166.2, C167.2, C168.2, C169.2, C170.2, C171.2, C172.2, C173.2, C174.2, C175.2, C176.2, C177.2, C178.2, C179.2, C180.2, C181.2, C182.2, C183.2, C184.2, C185.2, C186.2, C187.2, C188.2, C189.2, C190.2, C191.2, C192.2, C193.2, C194.2, C195.2, C196.2, C197.2, C198.2, C199.2, C200.2, C201.2, C202.2, C203.2, C204.2, C205.2, C206.2, C207.2, C208.2, C209.2, C210.2, C211.2, C212.2, C213.2, C214.2, C215.2, C216.2, C217.2, C218.2, C219.2, C220.2, C221.2, C222.2, C223.2, C224.2, C225.2, C226.2, C227.2, C228.2, C229.2, C230.2, C231.2, C232.2, C233.2, C234.2, D3.1 (VSS), D4.1 (VSS), D5.1 (VSS), D6.1 (VSS), D7.1 (VSS), D8.1 (VSS), D9.1 (VSS), D10.1 (VSS), D11.1 (VSS), D12.1 (VSS), D13.1 (VSS), D14.1 (VSS), D15.1 (VSS), D16.1 (VSS), D17.1 (VSS), D18.1 (VSS), D19.1 (VSS), D20.1 (VSS), D21.1 (VSS), D22.1 (VSS), D23.1 (VSS), D24.1 (VSS), D25.1 (VSS), D26.1 (VSS), D27.1 (VSS), D28.1 (VSS), D29.1 (VSS), D30.1 (VSS), D31.1 (VSS), D32.1 (VSS), D33.1 (VSS), D34.1 (VSS), D35.1 (VSS), D36.1 (VSS), D37.1 (VSS), D38.1 (VSS), D39.1 (VSS), D40.1 (VSS), D41.1 (VSS), D42.1 (VSS), D43.1 (VSS), D44.1 (VSS), D45.1 (VSS), D46.1 (VSS), D47.1 (VSS), D48.1 (VSS), D49.1 (VSS), D50.1 (VSS), D51.1 (VSS), D52.1 (VSS), D53.1 (VSS), D54.1 (VSS), D55.1 (VSS), D56.1 (VSS), D57.1 (VSS), D58.1 (VSS), D59.1 (VSS), D60.1 (VSS), D61.1 (VSS), D62.1 (VSS), D63.1 (VSS), D64.1 (VSS), D65.1 (VSS), D66.1 (VSS), D67.1 (VSS), D68.1 (VSS), D69.1 (VSS), D70.1 (VSS), D71.1 (VSS), D72.1 (VSS), D73.1 (VSS), D74.1 (VSS), D75.1 (VSS), D76.1 (VSS), D77.1 (VSS), D78.1 (VSS), D79.1 (VSS), D80.1 (VSS), D81.1 (VSS), D82.1 (VSS), D83.1 (VSS), D84.1 (VSS), D85.1 (VSS), D86.1 (VSS), D87.1 (VSS), D88.1 (VSS), D89.1 (VSS), D90.1 (VSS), D91.1 (VSS), D92.1 (VSS), D93.1 (VSS), D94.1 (VSS), D95.1 (VSS), D96.1 (VSS), D97.1 (VSS), D98.1 (VSS), D99.1 (VSS), D100.1 (VSS), D101.1 (VSS), D102.1 (VSS), D103.1 (VSS), D104.1 (VSS), D105.1 (VSS), D106.1 (VSS), D107.1 (VSS), D108.1 (VSS), D109.1 (VSS), D110.1 (VSS), D111.1 (VSS), D112.1 (VSS), D113.1 (VSS), D114.1 (VSS), D115.1 (VSS), D116.1 (VSS), D117.1 (VSS), D118.1 (VSS), D119.1 (VSS), D120.1 (VSS), D121.1 (VSS), D122.1 (VSS), D123.1 (VSS), D124.1 (VSS), D125.1 (VSS), D126.1 (VSS), D127.1 (VSS), D128.1 (VSS), D129.1 (VSS), D130.1 (VSS); also elsewhere on the board
LED_DATA_IN1: D3.2 (DIN), D4.2 (DIN), D5.2 (DIN), D15.2 (DIN), D16.2 (DIN), D23.2 (DIN), D24.2 (DIN), D25.2 (DIN), J17.1, J20.1; also elsewhere on the board
LED_DATA_IN2: D35.2 (DIN), D36.2 (DIN), D37.2 (DIN), D47.2 (DIN), D48.2 (DIN), D55.2 (DIN), D56.2 (DIN), D57.2 (DIN), J18.2, R20.1
LED_DATA_IN3: D67.2 (DIN), D68.2 (DIN), D69.2 (DIN), D79.2 (DIN), D80.2 (DIN), D87.2 (DIN), D88.2 (DIN), D89.2 (DIN), J17.3, R21.1
LED_DATA_IN4: D99.2 (DIN), D100.2 (DIN), D101.2 (DIN), D111.2 (DIN), D112.2 (DIN), D119.2 (DIN), D120.2 (DIN), D121.2 (DIN), J18.4, R22.1
LED_DATA_OUT1: D14.4 (DOUT), D22.4 (DOUT), J18.1, R20.2
LED_DATA_OUT2: D46.4 (DOUT), D54.4 (DOUT), J17.2, R21.2
LED_DATA_OUT3: D78.4 (DOUT), D86.4 (DOUT), J18.3, R22.2
LED_DATA_OUT4: D110.4 (DOUT), D118.4 (DOUT), J17.4, J19.1
unnamed: D8.4 (DOUT), D9.2 (DIN), D10.2 (DIN), D11.2 (DIN), D18.4 (DOUT), D19.2 (DIN), D20.2 (DIN), D29.2 (DIN), D30.2 (DIN), D31.2 (DIN)
unnamed: D11.4 (DOUT), D12.2 (DIN), D13.2 (DIN), D14.2 (DIN), D20.4 (DOUT), D21.2 (DIN), D22.2 (DIN), D32.2 (DIN), D33.2 (DIN), D34.2 (DIN)
unnamed: D5.4 (DOUT), D6.2 (DIN), D7.2 (DIN), D8.2 (DIN), D16.4 (DOUT), D17.2 (DIN), D18.2 (DIN), D26.2 (DIN), D27.2 (DIN), D28.2 (DIN)
unnamed: D37.4 (DOUT), D38.2 (DIN), D39.2 (DIN), D40.2 (DIN), D48.4 (DOUT), D49.2 (DIN), D50.2 (DIN), D58.2 (DIN), D59.2 (DIN), D60.2 (DIN)
unnamed: D40.4 (DOUT), D41.2 (DIN), D42.2 (DIN), D43.2 (DIN), D50.4 (DOUT), D51.2 (DIN), D52.2 (DIN), D61.2 (DIN), D62.2 (DIN), D63.2 (DIN)
unnamed: D43.4 (DOUT), D44.2 (DIN), D45.2 (DIN), D46.2 (DIN), D52.4 (DOUT), D53.2 (DIN), D54.2 (DIN), D64.2 (DIN), D65.2 (DIN), D66.2 (DIN)
unnamed: D69.4 (DOUT), D70.2 (DIN), D71.2 (DIN), D72.2 (DIN), D80.4 (DOUT), D81.2 (DIN), D82.2 (DIN), D90.2 (DIN), D91.2 (DIN), D92.2 (DIN)
unnamed: D72.4 (DOUT), D73.2 (DIN), D74.2 (DIN), D75.2 (DIN), D82.4 (DOUT), D83.2 (DIN), D84.2 (DIN), D93.2 (DIN), D94.2 (DIN), D95.2 (DIN)
unnamed: D75.4 (DOUT), D76.2 (DIN), D77.2 (DIN), D78.2 (DIN), D84.4 (DOUT), D85.2 (DIN), D86.2 (DIN), D96.2 (DIN), D97.2 (DIN), D98.2 (DIN)
unnamed: D101.4 (DOUT), D102.2 (DIN), D103.2 (DIN), D104.2 (DIN), D112.4 (DOUT), D113.2 (DIN), D114.2 (DIN), D122.2 (DIN), D123.2 (DIN), D124.2 (DIN)
unnamed: D104.4 (DOUT), D105.2 (DIN), D106.2 (DIN), D107.2 (DIN), D114.4 (DOUT), D115.2 (DIN), D116.2 (DIN), D125.2 (DIN), D126.2 (DIN), D127.2 (DIN)
unnamed: D107.4 (DOUT), D108.2 (DIN), D109.2 (DIN), D110.2 (DIN), D116.4 (DOUT), D117.2 (DIN), D118.2 (DIN), D128.2 (DIN), D129.2 (DIN), D130.2 (DIN)
